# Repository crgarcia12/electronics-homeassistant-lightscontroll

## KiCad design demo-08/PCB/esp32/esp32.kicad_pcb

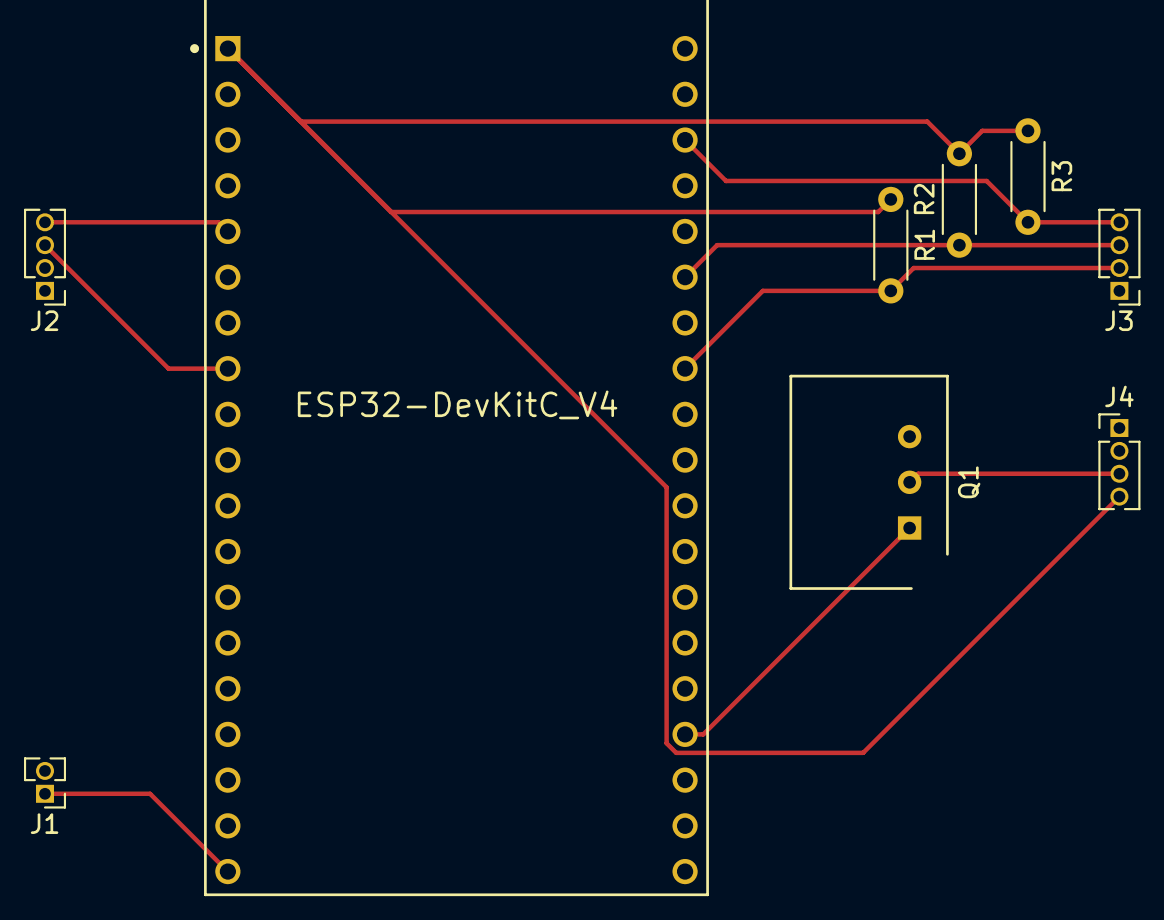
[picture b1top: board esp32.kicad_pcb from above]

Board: 2 copper layers, 9 parts (0 on the bottom side), 10 nets.

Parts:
J1: Conn_01x02_Female; PinHeader_1x02_P1.27mm_Vertical
J2, J3, J4: Conn_01x04_Female; PinHeader_1x04_P1.27mm_Vertical
MD1: ESP32-DevKitC_V4; Espressif-ESP32-DevKitC_V4-0-0-MFG
Q1: Q_NPN_BCE; SIP3_11.6x8.5mm
R1, R2, R3: 10k; R_Axial_DIN0204_L3.6mm_D1.6mm_P5.08mm_Horizontal

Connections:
3.3V: J4.4, MD1.1, R1.1, R2.1, R3.1
+1V5: J1.1, J2.1, J4.2, MD1.19
GND: J1.2, J2.2, J3.1, J4.1, MD1.14, Q1.3
unnamed: J2.3, MD1.8
unnamed: J2.4, MD1.5
unnamed: J3.2, MD1.31, R1.2
unnamed: J3.3, MD1.33, R2.2
unnamed: J3.4, MD1.36, R3.2
unnamed: J4.3, Q1.2
unnamed: MD1.23, Q1.1

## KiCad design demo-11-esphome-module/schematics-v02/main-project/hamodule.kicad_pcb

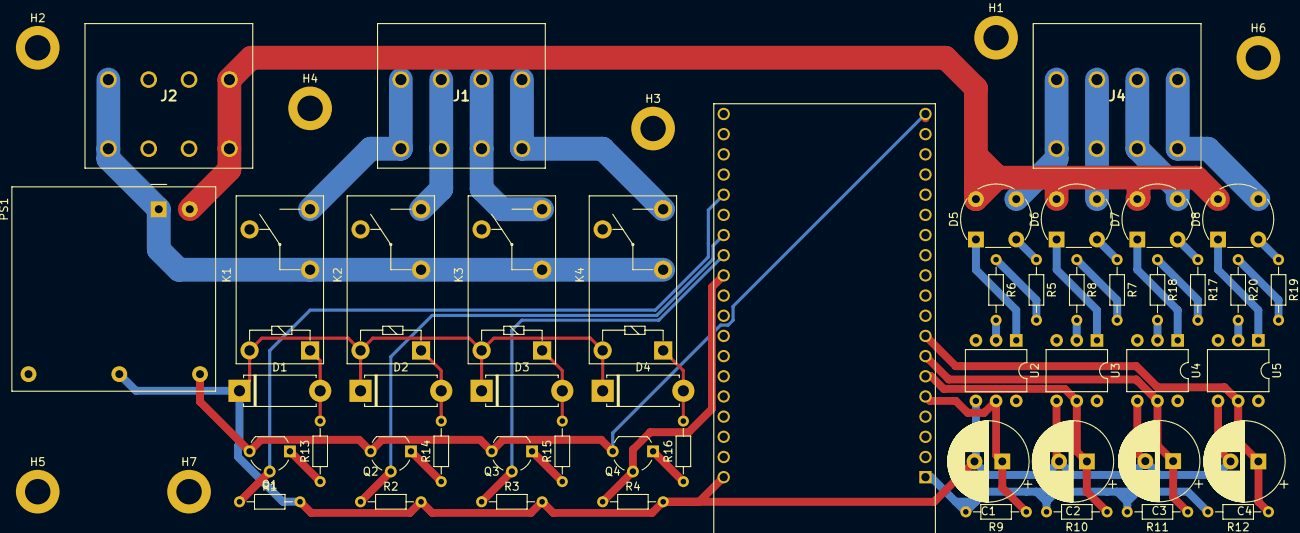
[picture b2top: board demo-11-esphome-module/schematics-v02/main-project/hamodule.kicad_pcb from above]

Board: 2 copper layers, 56 parts (0 on the bottom side), 46 nets.

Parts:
C1, C2, C3, C4: 4.7uF; CP_Radial_D10.0mm_P3.50mm
D1, D2, D3, D4: DIODE; D_5W_P10.16mm_Horizontal
D5, D6, D7, D8: D_Bridge_+-AA; Diode_Bridge_Round_D8.9mm
H1, H2, H3, H4, H5, H6, H7: MountingHole_Pad; MountingHole_3.2mm_M3_ISO14580_Pad
J1, J2, J4: 1017505
K1, K2, K3, K4: G5Q-1; Relay_SPDT_Omron-G5Q-1
PS1: RAC05-05SK; Converter_ACDC_RECOM_RAC05-xxSK_THT
Q1, Q2, Q3, Q4: 2N2219; TO-92_Wide
R1, R2, R3, R4, R9, R10, R11, R12: 10K; R_Axial_DIN0204_L3.6mm_D1.6mm_P7.62mm_Horizontal
R5, R6, R7, R8, R17, R18, R19, R20: 110k; R_Axial_DIN0204_L3.6mm_D1.6mm_P7.62mm_Horizontal
R13, R14, R15, R16: 220; R_Axial_DIN0204_L3.6mm_D1.6mm_P7.62mm_Horizontal
U1: ESP32-DEVKITC-32D; MODULE_ESP32-DEVKITC-32D
U2, U3, U4, U5: 4N35; DIP-6_W7.62mm

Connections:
3.3V+: R9.2, R10.2, R11.2, R12.2, U1.1
5V+: PS1.5, Q1.3, Q2.3, Q3.3, Q4.3, U1.19
5VGND: C1.2, C2.2, C3.2, C4.2, D1.1, D2.1, D3.1, D4.1, K1.5, K2.5, K3.5, K4.5, PS1.4, R1.2, R2.2, R3.2, R4.2, U1.20, U2.4, U3.4, U4.4, U5.4
220VAC(L): J2.7, J2.8, K1.2, K2.2, K3.2, K4.2, PS1.1
220VAC(N): D5.4, D6.4, D7.4, D8.4, J2.1, J2.2, PS1.2
Earth: H1.1, H2.1, H3.1, H4.1, H5.1, H6.1, H7.1, J2.3, J2.4, J2.5, J2.6
GPIO32: C3.1, R11.1, U1.7, U4.5
GPIO33: C4.1, R12.1, U1.8, U5.5
GPIO34: C1.1, R9.1, U1.5, U2.5
GPIO35: C2.1, R10.1, U1.6, U3.5
unnamed: D1.2, K1.1, R13.2
unnamed: D2.2, K2.1, R14.2
unnamed: D3.2, K3.1, R15.2
unnamed: D4.2, K4.1, R16.2
unnamed: D5.1, U2.1
unnamed: D5.2, R5.1
unnamed: D6.1, U3.1
unnamed: D6.2, R7.1
unnamed: D7.1, U4.1
unnamed: D7.2, R17.1
unnamed: D8.1, U5.1
unnamed: D8.2, R19.1
unnamed: Q1.1, R13.1
unnamed: Q1.2, R1.1, U1.34
unnamed: Q2.1, R14.1
unnamed: Q2.2, R2.1, U1.32
unnamed: Q3.1, R15.1
unnamed: Q3.2, R3.1, U1.31
unnamed: Q4.1, R16.1
unnamed: Q4.2, R4.1, U1.30
unnamed: R5.2, R6.1
unnamed: R6.2, U2.2
unnamed: R7.2, R8.1
unnamed: R8.2, U3.2
unnamed: R17.2, R18.1
unnamed: R18.2, U4.2
unnamed: R19.2, R20.1
unnamed: R20.2, U5.2
REO1: J1.7, J1.8, K1.3
REO2: J1.5, J1.6, K2.3
REO3: J1.3, J1.4, K3.3
REO4: J1.1, J1.2, K4.3
Sens1: D5.3, J4.7, J4.8
Sens2: D6.3, J4.5, J4.6
Sens3: D7.3, J4.3, J4.4
Sens4: D8.3, J4.1, J4.2

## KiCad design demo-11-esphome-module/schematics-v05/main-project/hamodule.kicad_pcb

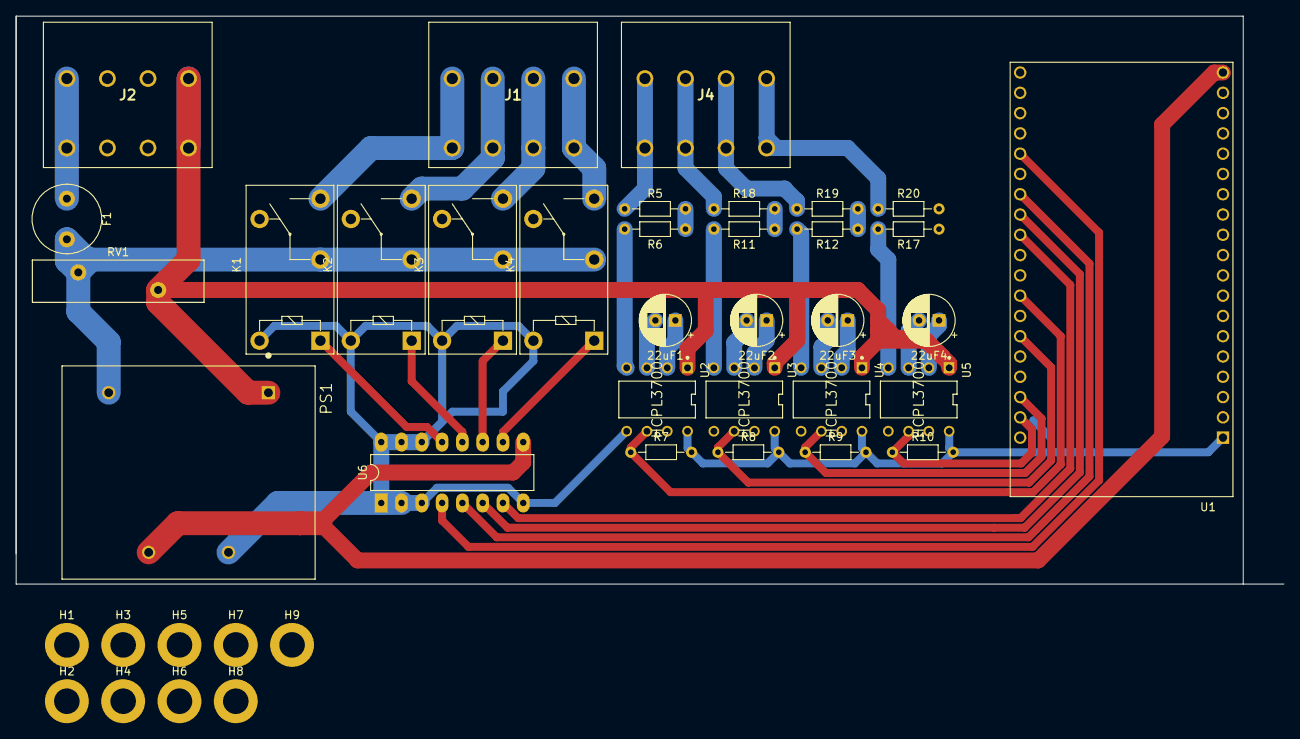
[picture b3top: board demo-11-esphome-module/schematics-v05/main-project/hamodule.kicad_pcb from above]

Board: 2 copper layers, 158.8 x 71.1 mm, 41 parts (0 on the bottom side), 42 nets.

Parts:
22uF1, 22uF2, 22uF3, 22uF4: CP_Small; CP_Radial_D6.3mm_P2.50mm
F1: Fuse; Fuse_Littelfuse_372_D8.50mm
H1, H2, H3, H4, H5, H6, H7, H8, H9: MountingHole_Pad; MountingHole_3.2mm_M3_ISO14580_Pad
J1, J2, J4: 1017505
K1, K2, K3, K4: G5Q-1; Relay_SPDT_Omron-G5Q-1
PS1: RAC05-05SK_277; 277
R5, R6, R11, R12, R17, R18, R19, R20: 47k; R_Axial_DIN0204_L3.6mm_D1.6mm_P7.62mm_Horizontal
R7, R8, R9, R10: 10K; R_Axial_DIN0204_L3.6mm_D1.6mm_P7.62mm_Horizontal
RV1: Varistor; RV_Disc_D21.5mm_W5.3mm_P10mm
U1: ESP32-DEVKITC-32D; MODULE_ESP32-DEVKITC-32D
U2, U3, U4, U5: HCPL3700; ON_Semi-CASE_62605_ISSUE_P-0-0-0
U6: ULN2003A; DIP-16_W7.62mm_LongPads

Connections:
3.3V+: R7.2, R8.2, R9.2, R10.2, U1.1, U2.8, U3.8, U4.8, U5.8
5V+: PS1.7, U1.19, U6.9
220VAC(L): F1.2, K1.2, K2.2, K3.2, K4.2, PS1.5, RV1.2
220VAC(N): J2.1, J2.2, PS1.1, RV1.1, U2.1, U3.1, U4.1, U5.1
GND(5V): K1.5, K2.5, K3.5, K4.5, PS1.9, U1.20, U2.5, U3.5, U4.5, U5.5, U6.1, U6.2, U6.3, U6.8, U6.14, U6.15, U6.16
GPIO19: U1.34, U6.4
GPIO21: U1.32, U6.5
GPIO22: U1.31, U6.6
GPIO23: U1.30, U6.7
GPIO32: R9.1, U1.22, U4.6
GPIO33: R10.1, U1.21, U5.6
GPIO34: R7.1, U1.27, U2.6
GPIO35: R8.1, U1.25, U3.6
unnamed: 22uF1.1, U2.2
unnamed: 22uF1.2, U2.3
unnamed: 22uF2.1, U3.2
unnamed: 22uF2.2, U3.3
unnamed: 22uF3.1, U4.2
unnamed: 22uF3.2, U4.3
unnamed: 22uF4.1, U5.2
unnamed: 22uF4.2, U5.3
unnamed: F1.1, J2.7, J2.8
unnamed: R5.2, R6.1
unnamed: R6.2, U2.4
unnamed: R11.1, R18.2
unnamed: R11.2, U3.4
unnamed: R12.1, R19.2
unnamed: R12.2, U4.4
unnamed: R17.1, R20.2
unnamed: R17.2, U5.4
REI1: K1.1, U6.13
REI2: K2.1, U6.12
REI3: K3.1, U6.11
REI4: K4.1, U6.10
REO1: J1.7, J1.8, K1.3
REO2: J1.5, J1.6, K2.3
REO3: J1.3, J1.4, K3.3
REO4: J1.1, J1.2, K4.3
Sens1: J4.7, J4.8, R5.1
Sens2: J4.5, J4.6, R18.1
Sens3: J4.3, J4.4, R19.1
Sens4: J4.1, J4.2, R20.1

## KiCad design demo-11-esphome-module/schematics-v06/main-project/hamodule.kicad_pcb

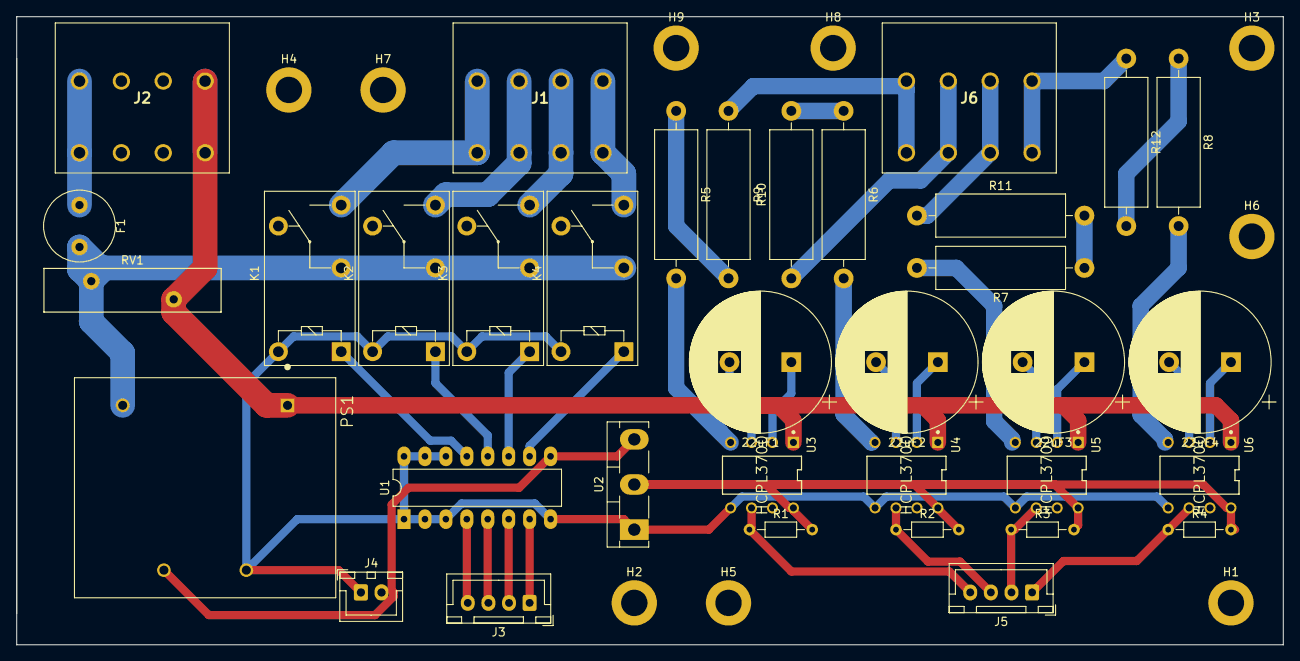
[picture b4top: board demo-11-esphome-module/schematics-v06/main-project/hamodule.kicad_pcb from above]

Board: 2 copper layers, 153.7 x 76.2 mm, 44 parts (0 on the bottom side), 39 nets.

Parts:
22uF1, 22uF2, 22uF3, 22uF4: CP_Small; CP_Radial_D17.0mm_P7.50mm
F1: Fuse; Fuse_Littelfuse_372_D8.50mm
H1, H2, H3, H4, H5, H6, H7, H8, H9: MountingHole_Pad; MountingHole_3.2mm_M3_ISO14580_Pad
J1, J2, J6: 1017505
J3: Conn-ESP-Relays; JST_XH_B4B-XH-A_1x04_P2.50mm_Vertical
J4: Conn_01x02; JST_XH_B2B-XH-A_1x02_P2.50mm_Vertical
J5: Conn-Esp-Sensors; JST_XH_B4B-XH-A_1x04_P2.50mm_Vertical
K1, K2, K3, K4: G5Q-1; Relay_SPDT_Omron-G5Q-1
PS1: RAC05-05SK_277; 277
R1, R2, R3, R4: 10K; R_Axial_DIN0204_L3.6mm_D1.6mm_P7.62mm_Horizontal
R5, R6, R7, R8, R9, R10, R11, R12: 47k; R_Axial_DIN0516_L15.5mm_D5.0mm_P20.32mm_Horizontal
RV1: Varistor; RV_Disc_D21.5mm_W5.3mm_P10mm
U1: ULN2003A; DIP-16_W7.62mm_LongPads
U2: LD1117S33TR_SOT223; TO-218-3_Vertical
U3, U4, U5, U6: HCPL3700; ON_Semi-CASE_62605_ISSUE_P-0-0-0

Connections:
3.3V+: R1.2, R2.2, R3.2, R4.2, U2.2, U3.8, U4.8, U5.8, U6.8
5V+: J4.2, PS1.7, U1.9, U2.3
220VAC(L): F1.2, K1.2, K2.2, K3.2, K4.2, PS1.5, RV1.2
220VAC(N): J2.1, J2.2, PS1.1, RV1.1, U3.1, U4.1, U5.1, U6.1
EspSens1: J5.4, R1.1, U3.6
EspSens2: J5.3, R2.1, U4.6
EspSens3: J5.2, R3.1, U5.6
EspSens4: J5.1, R4.1, U6.6
GND(5V): J4.1, K1.5, K2.5, K3.5, K4.5, PS1.9, U1.1, U1.2, U1.3, U1.8, U1.14, U1.15, U1.16, U2.1, U3.5, U4.5, U5.5, U6.5
unnamed: 22uF1.1, U3.2
unnamed: 22uF1.2, U3.3
unnamed: 22uF3.1, U5.2
unnamed: 22uF3.2, U5.3
unnamed: 22uF4.1, U6.2
unnamed: 22uF4.2, U6.3
unnamed: F1.1, J2.7, J2.8
unnamed: J3.1, U1.7
unnamed: J3.2, U1.6
unnamed: J3.3, U1.5
unnamed: J3.4, U1.4
unnamed: R5.1, R9.2
unnamed: R5.2, U3.4
unnamed: R7.2, U5.4
unnamed: R8.2, U6.4
unnamed: R6.1, R10.2
unnamed: R7.1, R11.2
unnamed: R8.1, R12.2
REI1: K1.1, U1.13
REI2: K2.1, U1.12
REI3: K3.1, U1.11
REI4: K4.1, U1.10
REO1: J1.7, J1.8, K1.3
REO2: J1.5, J1.6, K2.3
REO3: J1.3, J1.4, K3.3
REO4: J1.1, J1.2, K4.3
Sens1: J6.7, J6.8, R9.1
Sens2: J6.5, J6.6, R10.1
Sens3: J6.3, J6.4, R11.1
Sens4: J6.1, J6.2, R12.1

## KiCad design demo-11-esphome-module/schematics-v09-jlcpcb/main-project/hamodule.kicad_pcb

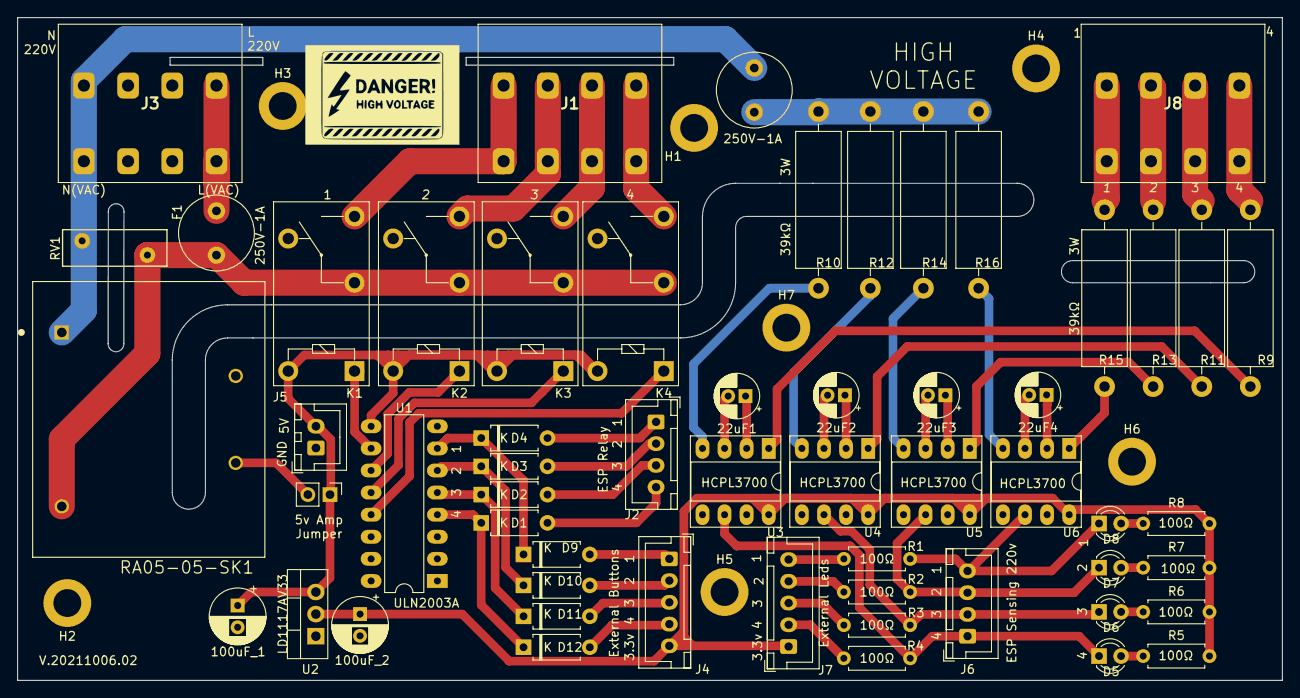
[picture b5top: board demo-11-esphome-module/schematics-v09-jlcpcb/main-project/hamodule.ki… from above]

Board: 2 copper layers, 145.4 x 76.2 mm, 64 parts (0 on the bottom side), 60 nets.

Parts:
22uF1, 22uF2, 22uF3, 22uF4: CP_Small; CP_Radial_D5.0mm_P2.00mm
100uF_1, 100uF_2: 100uF; CP_Radial_D6.3mm_P2.50mm
250V-1A: F250V; Fuse_Littelfuse_372_D8.50mm
D1, D2, D3, D4, D9, D10, D11, D12: D; D_A-405_P7.62mm_Horizontal
D5, D6, D7, D8: LED; LED_D3.0mm
F1: F250V; Fuse_Littelfuse_372_D8.50mm
H1, H2, H3, H4, H5, H6, H7: MountingHole_Pad; MountingHole_3.2mm_M3_ISO14580_Pad
J1, J3, J8: 1017505; 1017505_pretty
J2: Conn-ESP-Relays; JST_XH_B4B-XH-A_1x04_P2.50mm_Vertical
J4: Conn-Buttons; JST_XH_B5B-XH-A_1x05_P2.50mm_Vertical
J5: Conn_01x02; JST_XH_B2B-XH-A_1x02_P2.50mm_Vertical
J6: Conn-Esp-Sensors; JST_XH_B4B-XH-A_1x04_P2.50mm_Vertical
J7: Conn-LedIndicators; JST_XH_B5B-XH-A_1x05_P2.50mm_Vertical
J9: Current Jumper; PinHeader_1x02_P2.54mm_Vertical
K1, K2, K3, K4: G5Q-1; Relay_SPDT_Omron-G5Q-1
R1, R2, R3, R4, R5, R6, R7, R8: 100; R_Axial_DIN0207_L6.3mm_D2.5mm_P7.62mm_Horizontal
R9, R10, R11, R12, R13, R14, R15, R16: 39k2w; R_Axial_DIN0516_L15.5mm_D5.0mm_P20.32mm_Horizontal
RA05-05-SK1: RAC05-05SK_277; 277
RV1: Varistor250v; RV_Disc_D12mm_W4.2mm_P7.5mm
U1: ULN2003A; DIP-16_W7.62mm_LongPads
U2: LD1117S33TR_SOT223; TO-220-3_Vertical
U3, U4, U5, U6: HCPL3700; DIP-8_W7.62mm_Socket_LongPads

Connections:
3.3V+: 100uF_2.1, J4.5, J7.1, R5.2, R6.2, R7.2, R8.2, U2.2, U3.8, U4.8, U5.8, U6.8
5V+: 100uF_1.1, J5.2, J9.1, K1.5, K2.5, K3.5, K4.5, U1.9, U2.3
220VAC(L): F1.2, K1.2, K2.2, K3.2, K4.2, RA05-05-SK1.5, RV1.2
220VAC(N): 250V-1A.2, R10.1, R12.2, R14.1, R16.1
EspRel1: D1.1, D12.1, U1.4
EspRel2: D2.1, D11.1, U1.5
EspRel3: D3.1, D10.1, U1.6
EspRel4: D4.1, D9.1, U1.7
EspSens1: D8.1, J6.4, R1.1, U6.6
EspSens2: D7.1, J6.3, R2.1, U5.6
EspSens3: D6.1, J6.2, R3.1, U4.6
EspSens4: D5.1, J6.1, R4.1, U3.6
GND(5V): 100uF_1.2, 100uF_2.2, J5.1, RA05-05-SK1.9, U1.1, U1.2, U1.3, U1.8, U1.14, U1.15, U1.16, U2.1, U3.5, U4.5, U5.5, U6.5
unnamed: 22uF1.1, U3.2
unnamed: 22uF1.2, U3.3
unnamed: 22uF2.1, U4.2
unnamed: 22uF2.2, U4.3
unnamed: 22uF3.1, U5.2
unnamed: 22uF3.2, U5.3
unnamed: 22uF4.1, U6.2
unnamed: 22uF4.2, U6.3
unnamed: D1.2, J2.4
unnamed: D2.2, J2.3
unnamed: D3.2, J2.2
unnamed: D4.2, J2.1
unnamed: D5.2, R5.1
unnamed: D6.2, R6.1
unnamed: D7.2, R7.1
unnamed: D8.2, R8.1
unnamed: D9.2, J4.1
unnamed: D10.2, J4.2
unnamed: D11.2, J4.3
unnamed: D12.2, J4.4
unnamed: F1.1, J3.1, J3.2
unnamed: 250V-1A.1, J3.7, J3.8, RA05-05-SK1.1, RV1.1
unnamed: J7.2, R4.2
unnamed: J7.3, R3.2
unnamed: J7.4, R2.2
unnamed: J7.5, R1.2
unnamed: J9.2, RA05-05-SK1.7
unnamed: R9.2, U3.1
unnamed: R10.2, U3.4
unnamed: R11.1, U4.1
unnamed: R12.1, U4.4
unnamed: R13.2, U5.1
unnamed: R14.2, U5.4
unnamed: R15.2, U6.1
unnamed: R16.2, U6.4
REI1: K1.1, U1.10
REI2: K2.1, U1.11
REI3: K3.1, U1.12
REI4: K4.1, U1.13
REO1: J1.7, J1.8, K1.3
REO2: J1.5, J1.6, K2.3
REO3: J1.3, J1.4, K3.3
REO4: J1.1, J1.2, K4.3
Sens1: J8.5, J8.6, R13.1
Sens2: J8.7, J8.8, R15.1
Sens3: J8.3, J8.4, R11.2
Sens4: J8.1, J8.2, R9.1

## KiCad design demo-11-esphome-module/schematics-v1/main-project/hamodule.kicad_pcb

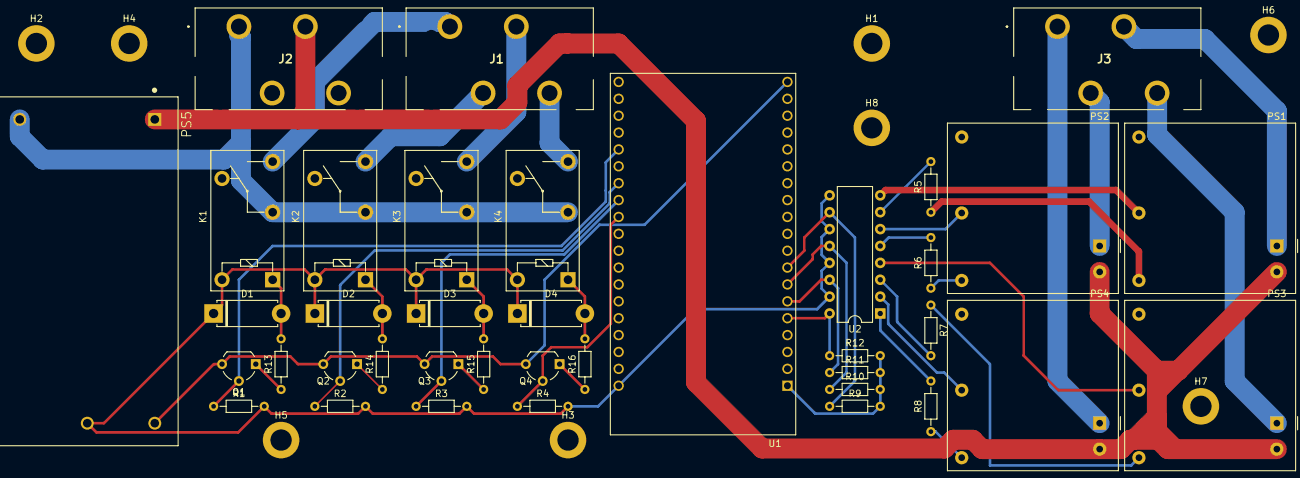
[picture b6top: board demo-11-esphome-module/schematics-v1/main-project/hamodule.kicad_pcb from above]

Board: 2 copper layers, 46 parts (0 on the bottom side), 42 nets.

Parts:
D1, D2, D3, D4: DIODE; D_5W_P10.16mm_Horizontal
H1, H2, H3, H4, H5, H6, H7, H8: MountingHole_Pad; MountingHole_3.2mm_M3_ISO14580_Pad
J1, J2, J3: 1864053
K1, K2, K3, K4: G5Q-1; Relay_SPDT_Omron-G5Q-1
PS1, PS2, PS3, PS4: RAC05-05SK; Converter_ACDC_RECOM_RAC05-xxSK_THT
PS5: RAC15-05SK; CONV_RAC15-05SK
Q1, Q2, Q3, Q4: 2N2219; TO-92_Wide
R1, R2, R3, R4, R9, R10, R11, R12: 10K; R_Axial_DIN0204_L3.6mm_D1.6mm_P7.62mm_Horizontal
R5, R6, R7, R8: 425; R_Axial_DIN0204_L3.6mm_D1.6mm_P7.62mm_Horizontal
R13, R14, R15, R16: 220; R_Axial_DIN0204_L3.6mm_D1.6mm_P7.62mm_Horizontal
U1: ESP32-DEVKITC-32D; MODULE_ESP32-DEVKITC-32D
U2: K847PH; DIP-16_W7.62mm

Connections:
3.3V+: R9.2, R10.2, R11.2, R12.2, U1.1
5V+: PS5.5, Q1.3, Q2.3, Q3.3, Q4.3, U1.19
5VGND: D1.1, D2.1, D3.1, D4.1, K1.5, K2.5, K3.5, K4.5, PS5.4, R1.2, R2.2, R3.2, R4.2, U1.20, U2.9, U2.11, U2.13, U2.15
220VAC(L): J2.1, K1.2, K2.2, K3.2, K4.2, PS5.2
220VAC(N): J2.3, PS1.2, PS2.2, PS3.2, PS4.2, PS5.1
Earth: H1.1, H2.1, H3.1, H4.1, H5.1, H6.1, H7.1, H8.1, J2.2, J2.4
unnamed: D1.2, K1.1, R13.2
unnamed: D2.2, K2.1, R14.2
unnamed: D3.2, K3.1, R15.2
unnamed: D4.2, K4.1, R16.2
unnamed: PS1.4, U2.8
unnamed: PS1.5, R5.1
unnamed: PS2.4, U2.6
unnamed: PS2.5, R6.1
unnamed: PS3.4, U2.4
unnamed: PS3.5, R7.1
unnamed: PS4.4, U2.2
unnamed: PS4.5, R8.1
unnamed: Q1.1, R13.1
unnamed: Q1.2, R1.1, U1.34
unnamed: Q2.1, R14.1
unnamed: Q2.2, R2.1, U1.32
unnamed: Q3.1, R15.1
unnamed: Q3.2, R3.1, U1.31
unnamed: Q4.1, R16.1
unnamed: Q4.2, R4.1, U1.30
unnamed: R5.2, U2.7
unnamed: R6.2, U2.5
unnamed: R7.2, U2.3
unnamed: R8.2, U2.1
unnamed: R9.1, U1.8, U2.10
unnamed: R10.1, U1.7, U2.12
unnamed: R11.1, U1.6, U2.14
unnamed: R12.1, U1.5, U2.16
REO1: J1.1, K1.3
REO2: J1.2, K2.3
REO3: J1.3, K3.3
REO4: J1.4, K4.3
Sens1: J3.1, PS4.1
Sens2: J3.2, PS2.1
Sens3: J3.3, PS1.1
Sens4: J3.4, PS3.1
